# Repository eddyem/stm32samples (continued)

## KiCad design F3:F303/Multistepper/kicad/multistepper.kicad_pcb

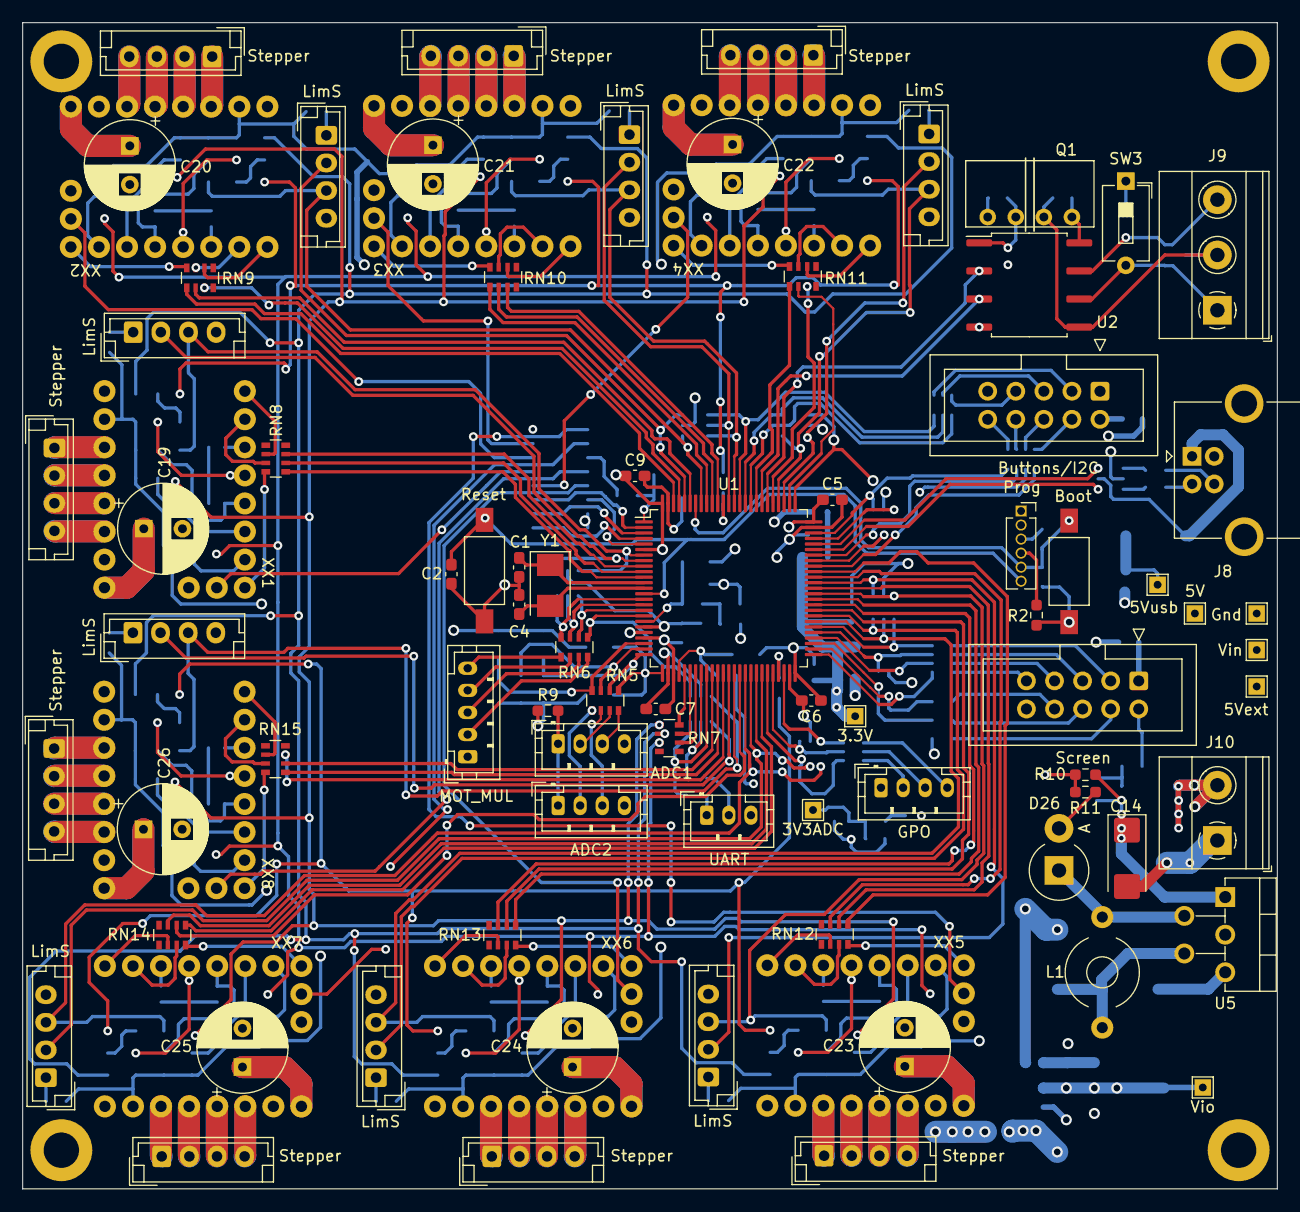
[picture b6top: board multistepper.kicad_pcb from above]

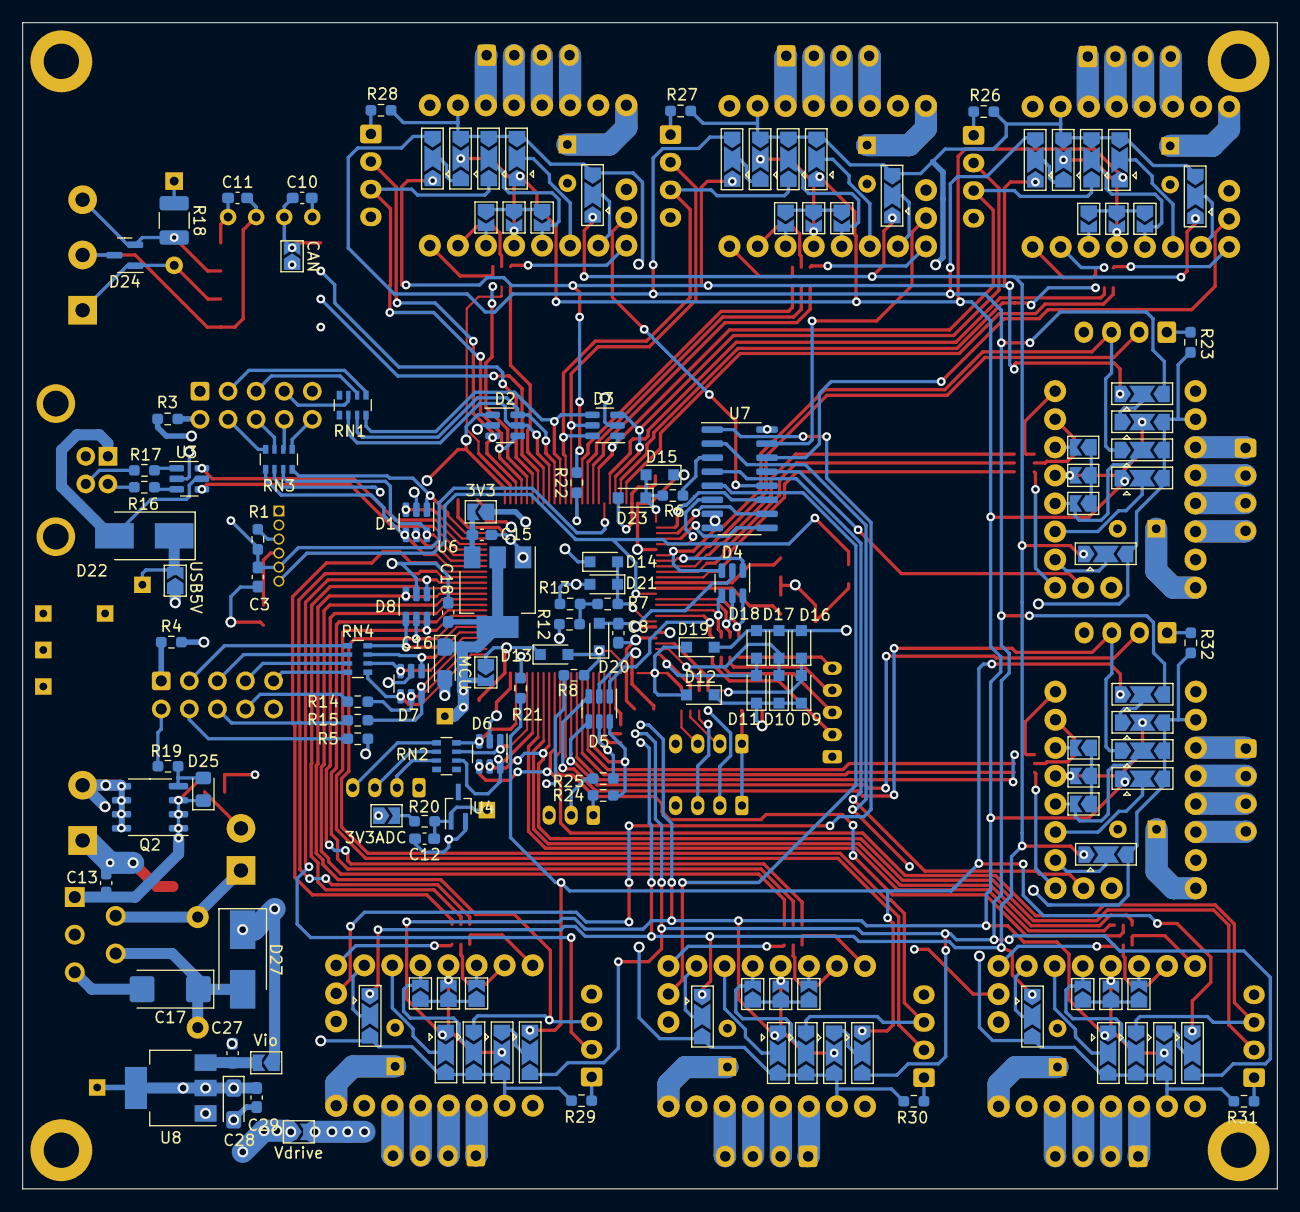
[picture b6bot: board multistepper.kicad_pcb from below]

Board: 4 copper layers, 113.5 x 105.5 mm, 236 parts (148 on the bottom side), 282 nets.

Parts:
C1, C4: 12; C_0603_1608Metric_Pad1.08x0.95mm_HandSolder
C2, C3, C5, C6, C7, C8, C9, C13, C15, C18, C27, C29: 0.1; C_0603_1608Metric_Pad1.08x0.95mm_HandSolder
C10, C11, C12: 1u; C_0603_1608Metric_Pad1.08x0.95mm_HandSolder
C14: 47u 35V; CP_EIA-6032-28_Kemet-C_Pad2.25x2.35mm_HandSolder
C16, C28: 47u 6V; CP_EIA-3216-18_Kemet-A_Pad1.58x1.35mm_HandSolder
C17: 47u 10V; CP_EIA-6032-28_Kemet-C_Pad2.25x2.35mm_HandSolder
C19, C20, C21, C22, C23, C24, C25, C26: 100u 35V; CP_Radial_D8.0mm_P3.50mm
D1, D2, D3, D4, D5, D6, D7, D8: SP0505BAHT; SOT-23-6
D9, D10, D11, D12, D13, D14, D15, D16, D17, D18, D19, D20, D21, D23: SS14; D_SOD-323_HandSoldering
D22, D27: MBRS130L; D_SMB_Handsoldering
D24: PESD1CAN; SOT-23
D25: MM3Z7V5; D_0805_2012Metric_Pad1.15x1.40mm_HandSolder
D26: 1N5822; D_DO-201_P3.81mm_Vertical_AnodeUp
H1, H2, H3, H4: MountingHole; MountingHole_3.2mm_M3_DIN965_Pad
J1: Prog; PinSocket_1x06_P1.27mm_Vertical
J2: Buttons/I2C; IDC-Header_2x05_P2.54mm_Vertical
J3: Screen; IDC-Header_2x05_P2.54mm_Vertical
J4: ADC2; JST_PH_B4B-PH-K_1x04_P2.00mm_Vertical
J5: ADC1; JST_PH_B4B-PH-K_1x04_P2.00mm_Vertical
J6: MOT_MUL; JST_PH_B5B-PH-K_1x05_P2.00mm_Vertical
J7: GPO; JST_PH_B4B-PH-K_1x04_P2.00mm_Vertical
J8: USB_B; USB_B_OST_USB-B1HSxx_Horizontal
J9: Screw_Terminal_01x03; TerminalBlock_Phoenix_MKDS-1,5-3_1x03_P5.00mm_Horizontal
J10: Screw_Terminal_01x02; TerminalBlock_Phoenix_MKDS-1,5-2_1x02_P5.00mm_Horizontal
J11, J14, J16, J18, J20, J22, J24, J26: LimS; JST_EH_B4B-EH-A_1x04_P2.50mm_Vertical
J12, J15, J17, J19, J21, J23, J25, J27: Stepper; JST_EH_B4B-EH-A_1x04_P2.50mm_Vertical
J13: UART; JST_PH_B3B-PH-K_1x03_P2.00mm_Vertical
JP1: CAN; SolderJumper-2_P1.3mm_Open_TrianglePad1.0x1.5mm
JP2: USB5V; SolderJumper-2_P1.3mm_Open_TrianglePad1.0x1.5mm
JP3: MCU; SolderJumper-2_P1.3mm_Open_TrianglePad1.0x1.5mm
JP4: 3V3ADC; SolderJumper-2_P1.3mm_Open_TrianglePad1.0x1.5mm
JP5: 3V3; SolderJumper-2_P1.3mm_Open_TrianglePad1.0x1.5mm
JP6: Vdrive; SolderJumper-2_P1.3mm_Open_TrianglePad1.0x1.5mm
JP7: Vio; SolderJumper-2_P1.3mm_Open_TrianglePad1.0x1.5mm
JP8, JP9, JP10, JP11, JP12, JP16, JP17, JP18, JP19, JP20, JP24, JP25, JP26, JP27, JP28, JP32, JP33, JP34, JP35, JP36, JP40, JP41, JP42, JP43, JP44, JP48, JP49, JP50, JP51, JP52, JP56, JP57, JP58, JP59, JP60, JP64, JP65, JP66, JP67, JP68: SolderJumper_3_Open; SolderJumper-3_P2.0mm_Open_TrianglePad1.0x1.5mm
JP13, JP14, JP15, JP21, JP22, JP23, JP29, JP30, JP31, JP37, JP38, JP39, JP45, JP46, JP47, JP53, JP54, JP55, JP61, JP62, JP63, JP69, JP70, JP71: SolderJumper_2_Bridged; SolderJumper-2_P1.3mm_Open_TrianglePad1.0x1.5mm
L1: 100u; L_Toroid_Horizontal_D6.5mm_P10.00mm_Diameter7-5mm_Amidon-T25
Q1: B0505S; B0x0xS
Q2: IRF9310; SO-8_3.9x4.9mm_P1.27mm
R1, R11: 10k; R_0603_1608Metric_Pad0.98x0.95mm_HandSolder
R2, R3, R9, R16, R17, R24, R25: 22; R_0603_1608Metric_Pad0.98x0.95mm_HandSolder
R4: 7.5; R_0603_1608Metric_Pad0.98x0.95mm_HandSolder
R5: 5.1; R_0603_1608Metric_Pad0.98x0.95mm_HandSolder
R6, R7, R8, R14, R15: 330; R_0603_1608Metric_Pad0.98x0.95mm_HandSolder
R10: 91k; R_0603_1608Metric_Pad0.98x0.95mm_HandSolder
R12, R13: 47k; R_0603_1608Metric_Pad0.98x0.95mm_HandSolder
R18: 120; R_1210_3225Metric_Pad1.30x2.65mm_HandSolder
R19, R20: 4k7; R_0603_1608Metric_Pad0.98x0.95mm_HandSolder
R21, R22, R23, R26, R27, R28, R29, R30, R31, R32: 100; R_0603_1608Metric_Pad0.98x0.95mm_HandSolder
RN1, RN2, RN3, RN4, RN5, RN6, RN7, RN8, RN9, RN10, RN11, RN12, RN13, RN14, RN15: 330; R_Array_Convex_4x0603
SW1: Reset; SW_SPST_FSMSM
SW2: Boot; SW_SPST_FSMSM
SW3: SW_DIP_x01; SW_DIP_SPSTx01_Slide_6.7x4.1mm_W7.62mm_P2.54mm_LowProfile
TP1: 5Vusb; TestPoint_THTPad_1.5x1.5mm_Drill0.7mm
TP2: Vin; TestPoint_THTPad_1.5x1.5mm_Drill0.7mm
TP3: Gnd; TestPoint_THTPad_1.5x1.5mm_Drill0.7mm
TP4: 5Vext; TestPoint_THTPad_1.5x1.5mm_Drill0.7mm
TP5: 3.3V; TestPoint_THTPad_1.5x1.5mm_Drill0.7mm
TP6: 3V3ADC; TestPoint_THTPad_1.5x1.5mm_Drill0.7mm
TP7: 5V; TestPoint_THTPad_1.5x1.5mm_Drill0.7mm
TP8: Vio; TestPoint_THTPad_1.5x1.5mm_Drill0.7mm
U1: STM32F303VDTx; LQFP-100_14x14mm_P0.5mm
U2: ISO1050DUB; SOP-8_6.62x9.15mm_P2.54mm
U3: USBLC6-2SC6; SOT-23-6
U4: LM4050A(b)EX3-3.3; SOT-323_SC-70_Handsoldering
U5: LM2576-5.0; TO-220-5_P3.4x3.7mm_StaggerEven_Lead3.8mm_Vertical
U6, U8: LM1117-3.3; SOT-223-3_TabPin2
U7: 74HC4051; SOIC-16_3.9x9.9mm_P1.27mm
XX1, XX2, XX3, XX4, XX5, XX6, XX7, XX8: stepper_module
Y1: NX5032GA-8MHz; Crystal_SMD_5032-2Pin_5.0x3.2mm

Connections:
+3.3VADC: C12.1, R20.1, TP6.1, U1.21 (VREF+), U4.1 (K)
+3V3: C16.1, C18.1, JP3.2 (B), R3.2, R4.2, TP5.1, U6.2 (VO)
+5V: D27.1 (K), JP1.1 (A), JP2.1 (A), JP4.1 (A), JP5.1 (A), JP7.1 (A), R5.1, R12.2, TP7.1
/CANH: D24.2 (K), J9.3, R18.2, U2.7 (CANH)
/CANL: D24.1 (K), J9.1, SW3.2, U2.6 (CANL)
/MCU base/A0: D9.2 (A), D16.1 (K), RN5.8 (R1.2), U1.23 (PA0)
/MCU base/A1: D10.2 (A), D17.1 (K), RN5.7 (R2.2), U1.24 (PA1)
/MCU base/A2: D11.2 (A), D18.1 (K), RN5.6 (R3.2), U1.25 (PA2)
/MCU base/A3: D12.2 (A), D19.1 (K), RN5.5 (R4.2), U1.26 (PA3)
/MCU base/A4: D13.2 (A), D20.1 (K), R8.1, U1.29 (PA4)
/MCU base/A5: D14.2 (A), D21.1 (K), R7.2, U1.19 (PF2)
/MCU base/BOOT0: C3.1, J1.5, R1.1, SW2.1, U1.94 (BOOT0)
/MCU base/BTN0: D1.4 (K), RN3.1 (R1.1), U1.67 (PA8)
/MCU base/BTN1: D1.5 (K), RN3.2 (R2.1), U1.68 (PA9)
/MCU base/BTN2_SDA: D1.6 (K), RN3.3 (R3.1), U1.69 (PA10)
/MCU base/BTN3_SCL: D1.1 (K), RN3.4 (R4.1), U1.73 (PF6)
/MCU base/BTN4: D2.5 (K), RN1.6 (R3.2), U1.84 (PD3)
/MCU base/BTN5: D2.6 (K), RN1.7 (R2.2), U1.85 (PD4)
/MCU base/BTN6: D3.4 (K), RN1.8 (R1.2), U1.86 (PD5)
/MCU base/Diagn: D15.2 (A), D23.1 (K), R6.2, U1.1 (PE2)
/MCU base/MOT_MUL0: D4.6 (K), RN6.8 (R1.2), U1.15 (PC0)
/MCU base/MOT_MUL1: D4.5 (K), RN6.7 (R2.2), U1.16 (PC1)
/MCU base/MOT_MUL2: D4.4 (K), RN6.6 (R3.2), U1.17 (PC2)
/MCU base/MOT_MUL_EN: D5.1 (K), RN6.5 (R4.2), U1.18 (PC3)
/MCU base/NRST: C2.1, J1.6, SW1.1, U1.14 (NRST)
/MCU base/OSC_IN: C1.1, U1.12 (PF0), Y1.1
/MCU base/OSC_OUT: C4.1, U1.13 (PF1), Y1.2
/MCU base/OUT0: D6.3 (K), RN2.8 (R1.2), U1.48 (PB11)
/MCU base/OUT1: D6.1 (K), RN2.7 (R2.2), U1.46 (PE15)
/MCU base/OUT2: D6.6 (K), RN2.6 (R3.2), U1.45 (PE14)
/MCU base/SCRN_CS: D8.4 (K), RN4.4 (R4.1), U1.56 (PD9)
/MCU base/SCRN_DCRS: D7.4 (K), RN4.1 (R1.1), U1.51 (PB12)
/MCU base/SCRN_MISO: D7.6 (K), R15.1, U1.53 (PB14)
/MCU base/SCRN_MOSI: D7.3 (K), RN4.2 (R2.1), U1.54 (PB15)
/MCU base/SCRN_RST: D7.1 (K), RN4.3 (R3.1), U1.55 (PD8)
/MCU base/SCRN_SCK: D7.5 (K), R14.1, U1.52 (PB13)
/MCU base/SWCLK: D2.1 (K), J1.1, U1.76 (PA14)
/MCU base/SWDIO: D1.3 (K), J1.2, U1.72 (PA13)
/MCU base/USART1_RX: D5.6 (K), R24.1, U1.34 (PC5)
/MCU base/USART1_TX: D5.5 (K), R25.1, U1.33 (PC4)
/Motors/DIAG0: U7.13 (Y0), XX1.17 (DIAG)
/Motors/DIAG1: U7.14 (Y1), XX2.17 (DIAG)
/Motors/DIAG2: U7.15 (Y2), XX3.17 (DIAG)
/Motors/DIAG3: U7.12 (Y3), XX4.17 (DIAG)
/Motors/DIAG4: U7.1 (Y4), XX5.17 (DIAG)
/Motors/DIAG5: U7.5 (Y5), XX6.17 (DIAG)
/Motors/DIAG6: U7.2 (Y6), XX7.17 (DIAG)
/Motors/DIAG7: U7.4 (Y7), XX8.17 (DIAG)
/Motors/MISO: JP9.3 (B), JP17.3 (B), JP25.3 (B), JP33.3 (B), JP41.3 (B), JP49.3 (B), JP57.3 (B), JP65.3 (B), RN7.2 (R2.1)
/Motors/MOSI: JP10.1 (A), JP18.1 (A), JP26.1 (A), JP34.1 (A), JP42.1 (A), JP50.1 (A), JP58.1 (A), JP66.1 (A), RN7.3 (R3.1)
/Motors/SCK: JP11.1 (A), JP19.1 (A), JP27.1 (A), JP35.1 (A), JP43.1 (A), JP51.1 (A), JP59.1 (A), JP67.1 (A), RN7.1 (R1.1)
/Motors/USART0-3: JP9.1 (A), JP17.1 (A), JP25.1 (A), JP33.1 (A), R22.2
/Motors/USART4-7: JP41.1 (A), JP49.1 (A), JP57.1 (A), JP65.1 (A), R21.2
/Motors/Vm: C19.1, C20.1, C21.1, C22.1, C23.1, C24.1, C25.1, C26.1, JP6.2 (B), XX1.16 (Vmot), XX2.16 (Vmot), XX3.16 (Vmot), XX4.16 (Vmot), XX5.16 (Vmot), XX6.16 (Vmot), XX7.16 (Vmot), XX8.16 (Vmot)
/Motors/stepper_M1/CLK: JP15.2 (B), XX1.6 (CLK)
/Motors/stepper_M1/DIRx: RN8.2 (R2.1), XX1.8 (DIR)
/Motors/stepper_M1/MS1: JP10.2 (C), XX1.2 (MS1)
/Motors/stepper_M1/MS2: JP11.2 (C), XX1.3 (MS2)
/Motors/stepper_M1/SPR: JP12.2 (C), JP13.2 (B), XX1.4 (SPREAD)
/Motors/stepper_M1/STEPx: RN8.3 (R3.1), XX1.7 (STEP)
/Motors/stepper_M1/U: JP8.2 (C), JP14.2 (B), XX1.5 (PDN_UART)
/Motors/stepper_M1/~ENx: RN8.4 (R4.1), XX1.1 (~EN)
/Motors/stepper_M2/CLK: JP23.2 (B), XX2.6 (CLK)
/Motors/stepper_M2/DIRx: RN9.2 (R2.1), XX2.8 (DIR)
/Motors/stepper_M2/MS1: JP18.2 (C), XX2.2 (MS1)
/Motors/stepper_M2/MS2: JP19.2 (C), XX2.3 (MS2)
/Motors/stepper_M2/SPR: JP20.2 (C), JP21.2 (B), XX2.4 (SPREAD)
/Motors/stepper_M2/STEPx: RN9.3 (R3.1), XX2.7 (STEP)
/Motors/stepper_M2/U: JP16.2 (C), JP22.2 (B), XX2.5 (PDN_UART)
/Motors/stepper_M2/~ENx: RN9.4 (R4.1), XX2.1 (~EN)
/Motors/stepper_M3/CLK: JP31.2 (B), XX3.6 (CLK)
/Motors/stepper_M3/DIRx: RN10.2 (R2.1), XX3.8 (DIR)
/Motors/stepper_M3/MS1: JP26.2 (C), XX3.2 (MS1)
/Motors/stepper_M3/MS2: JP27.2 (C), XX3.3 (MS2)
/Motors/stepper_M3/SPR: JP28.2 (C), JP29.2 (B), XX3.4 (SPREAD)
/Motors/stepper_M3/STEPx: RN10.3 (R3.1), XX3.7 (STEP)
/Motors/stepper_M3/U: JP24.2 (C), JP30.2 (B), XX3.5 (PDN_UART)
/Motors/stepper_M3/~ENx: RN10.4 (R4.1), XX3.1 (~EN)
/Motors/stepper_M4/CLK: JP39.2 (B), XX4.6 (CLK)
/Motors/stepper_M4/DIRx: RN11.2 (R2.1), XX4.8 (DIR)
/Motors/stepper_M4/MS1: JP34.2 (C), XX4.2 (MS1)
/Motors/stepper_M4/MS2: JP35.2 (C), XX4.3 (MS2)
/Motors/stepper_M4/SPR: JP36.2 (C), JP37.2 (B), XX4.4 (SPREAD)
/Motors/stepper_M4/STEPx: RN11.3 (R3.1), XX4.7 (STEP)
/Motors/stepper_M4/U: JP32.2 (C), JP38.2 (B), XX4.5 (PDN_UART)
/Motors/stepper_M4/~ENx: RN11.4 (R4.1), XX4.1 (~EN)
/Motors/stepper_M5/CLK: JP47.2 (B), XX5.6 (CLK)
/Motors/stepper_M5/DIRx: RN12.2 (R2.1), XX5.8 (DIR)
/Motors/stepper_M5/MS1: JP42.2 (C), XX5.2 (MS1)
/Motors/stepper_M5/MS2: JP43.2 (C), XX5.3 (MS2)
/Motors/stepper_M5/SPR: JP44.2 (C), JP45.2 (B), XX5.4 (SPREAD)
/Motors/stepper_M5/STEPx: RN12.3 (R3.1), XX5.7 (STEP)
/Motors/stepper_M5/U: JP40.2 (C), JP46.2 (B), XX5.5 (PDN_UART)
/Motors/stepper_M5/~ENx: RN12.4 (R4.1), XX5.1 (~EN)
/Motors/stepper_M6/CLK: JP55.2 (B), XX6.6 (CLK)
/Motors/stepper_M6/DIRx: RN13.2 (R2.1), XX6.8 (DIR)
/Motors/stepper_M6/MS1: JP50.2 (C), XX6.2 (MS1)
/Motors/stepper_M6/MS2: JP51.2 (C), XX6.3 (MS2)
/Motors/stepper_M6/SPR: JP52.2 (C), JP53.2 (B), XX6.4 (SPREAD)
/Motors/stepper_M6/STEPx: RN13.3 (R3.1), XX6.7 (STEP)
/Motors/stepper_M6/U: JP48.2 (C), JP54.2 (B), XX6.5 (PDN_UART)
/Motors/stepper_M6/~ENx: RN13.4 (R4.1), XX6.1 (~EN)
/Motors/stepper_M7/CLK: JP63.2 (B), XX7.6 (CLK)
/Motors/stepper_M7/DIRx: RN14.2 (R2.1), XX7.8 (DIR)
/Motors/stepper_M7/MS1: JP58.2 (C), XX7.2 (MS1)
/Motors/stepper_M7/MS2: JP59.2 (C), XX7.3 (MS2)
/Motors/stepper_M7/SPR: JP60.2 (C), JP61.2 (B), XX7.4 (SPREAD)
/Motors/stepper_M7/STEPx: RN14.3 (R3.1), XX7.7 (STEP)
/Motors/stepper_M7/U: JP56.2 (C), JP62.2 (B), XX7.5 (PDN_UART)
/Motors/stepper_M7/~ENx: RN14.4 (R4.1), XX7.1 (~EN)
/Motors/stepper_M8/CLK: JP71.2 (B), XX8.6 (CLK)
/Motors/stepper_M8/DIRx: RN15.2 (R2.1), XX8.8 (DIR)
/Motors/stepper_M8/MS1: JP66.2 (C), XX8.2 (MS1)
/Motors/stepper_M8/MS2: JP67.2 (C), XX8.3 (MS2)
/Motors/stepper_M8/SPR: JP68.2 (C), JP69.2 (B), XX8.4 (SPREAD)
/Motors/stepper_M8/STEPx: RN15.3 (R3.1), XX8.7 (STEP)
/Motors/stepper_M8/U: JP64.2 (C), JP70.2 (B), XX8.5 (PDN_UART)
/Motors/stepper_M8/~ENx: RN15.4 (R4.1), XX8.1 (~EN)
/VB: D22.2 (A), J8.1 (VBUS), U3.5 (VBUS)
ADC0: J4.2, RN5.1 (R1.1)
ADC1: J4.3, RN5.2 (R2.1)
ADC2: J5.2, RN5.3 (R3.1)
ADC3: J5.3, RN5.4 (R4.1)
ADC4: R8.2, R10.1, R11.2
ADC5: R7.1, R12.1, R13.2
CAN_RX: U1.81 (PD0), U2.2 (RXD)
CAN_TX: U1.82 (PD1), U2.3 (TXD)
DIAGNOST: R6.1, U7.3 (Z)
Earth: C11.2, D24.3 (O), J9.2, Q1.3 (0V), U2.5 (GND2)
GND: C1.2, C2.2, C4.2, C5.2, C6.2, C7.2, C8.2, C9.2, C10.2, C12.2, C13.2, C14.2, C15.2, C16.2, C17.2, C18.2, C19.2, C20.2, C21.2, C22.2, C23.2, C24.2, C25.2, C26.2, C27.2, C28.2, C29.2, D1.2 (A), D2.2 (A), D3.2 (A), D4.2 (A), D5.2 (A), D6.2 (A), D7.2 (A), D8.2 (A), D16.2 (A), D17.2 (A), D18.2 (A), D19.2 (A), D20.2 (A), D21.2 (A), D23.2 (A), D26.2 (A), J1.3, J2.1, J2.9, J3.2, J3.10, J4.4, J5.4, J6.1, J7.1, J8.4 (GND), J8.5 (Shield), J10.1, J11.4, J13.3, J14.4, J16.4, J18.4, J20.4, J22.4, J24.4, J26.4, Q1.1 (GND), R1.2, R11.1, R13.1, R19.2, SW1.2, TP3.1, U1.20 (VSSA), U1.27 (VSS), U1.49 (VSS), U1.74 (VSS), U1.99 (VSS), U2.4 (GND1), U3.2 (GND), U4.2 (A), U5.3 (GND), U5.5 (ON/OFF), U6.1 (GND), U7.7 (VEE), U7.8 (GND), U8.1 (GND), XX1.9 (GND), XX1.15 (GND), XX2.9 (GND), XX2.15 (GND), XX3.9 (GND), XX3.15 (GND), XX4.9 (GND), XX4.15 (GND), XX5.9 (GND), XX5.15 (GND), XX6.9 (GND), XX6.15 (GND), XX7.9 (GND), XX7.15 (GND), XX8.9 (GND), XX8.15 (GND)
M0_DIR: RN8.7 (R2.2), U1.9 (PC15)
M0_EN: RN8.5 (R4.2), U1.11 (PF10)
M0_L0: D4.1 (K), J11.2, U1.8 (PC14)
M0_L1: D4.3 (K), J11.3, JP12.1 (A), U1.7 (PC13)
M0_STEP: RN8.6 (R3.2), U1.10 (PF9)
M1_DIR: RN9.7 (R2.2), U1.97 (PE0)
M1_EN: RN9.5 (R4.2), U1.98 (PE1)
M1_L0: D3.3 (K), J14.2, U1.96 (PB9)
M1_L1: D3.1 (K), J14.3, JP20.1 (A), U1.93 (PB7)
M1_STEP: RN9.6 (R3.2), U1.95 (PB8)
M2_DIR: RN10.7 (R2.2), U1.90 (PB4)
M2_EN: RN10.5 (R4.2), U1.92 (PB6)
M2_L0: D3.5 (K), J16.2, U1.88 (PD7)
M2_L1: D3.6 (K), J16.3, JP28.1 (A), U1.87 (PD6)
M2_STEP: RN10.6 (R3.2), U1.91 (PB5)
M3_DIR: RN11.7 (R2.2), U1.80 (PC12)
M3_EN: RN11.5 (R4.2), U1.83 (PD2)
M3_L0: D2.3 (K), J18.2, U1.78 (PC10)
M3_L1: D2.4 (K), J18.3, JP36.1 (A), U1.79 (PC11)
M3_STEP: RN11.6 (R3.2), U1.77 (PA15)
M4_DIR: RN12.7 (R2.2), U1.65 (PC8)
M4_EN: RN12.5 (R4.2), U1.66 (PC9)
M4_L0: D8.1 (K), J20.2, U1.64 (PC7)
M4_L1: D8.3 (K), J20.3, JP44.1 (A), U1.62 (PD15)
M4_STEP: RN12.6 (R3.2), U1.63 (PC6)
M5_DIR: RN13.7 (R2.2), U1.60 (PD13)
M5_EN: RN13.5 (R4.2), U1.61 (PD14)
M5_L0: D8.6 (K), J22.2, U1.58 (PD11)
M5_L1: D8.5 (K), J22.3, JP52.1 (A), U1.57 (PD10)
M5_STEP: RN13.6 (R3.2), U1.59 (PD12)
M6_DIR: RN14.7 (R2.2), U1.43 (PE12)
M6_EN: RN14.5 (R4.2), U1.44 (PE13)
M6_L0: D6.5 (K), J24.2, U1.42 (PE11)
M6_L1: D6.4 (K), J24.3, JP60.1 (A), U1.41 (PE10)
M6_STEP: RN14.6 (R3.2), U1.40 (PE9)
M7_DIR: RN15.7 (R2.2), U1.37 (PB2)
M7_EN: RN15.5 (R4.2), U1.36 (PB1)
M7_L0: D5.4 (K), J26.2, U1.38 (PE7)
M7_L1: D5.3 (K), J26.3, JP68.1 (A), U1.39 (PE8)
M7_STEP: RN15.6 (R3.2), U1.35 (PB0)
MCU3v3: C3.2, C5.1, C6.1, C7.1, C8.1, C9.1, D9.1 (K), D10.1 (K), D11.1 (K), D12.1 (K), D13.1 (K), D14.1 (K), D15.1 (K), JP3.1 (A), R2.1, R9.1, SW2.2, U1.6 (VBAT), U1.22 (VDDA), U1.28 (VDD), U1.50 (VDD), U1.75 (VDD), U1.100 (VDD)
MUL0: U1.2 (PE3), U7.11 (S0)
MUL1: U1.3 (PE4), U7.10 (S1)
MUL2: U1.4 (PE5), U7.9 (S2)
MUL_EN: U1.5 (PE6), U7.6 (~E)
unnamed: C10.1, JP1.2 (B), Q1.2 (Vin), U2.1 (VCC1)
unnamed: C11.1, Q1.4 (+Vo), U2.8 (VCC2)
unnamed: C15.1, JP5.2 (B), U6.3 (VI)
unnamed: C17.1, D27.2 (A), L1.1, TP4.1, U5.4 (FB)
unnamed: C27.1, JP7.2 (B), U8.3 (VI)
unnamed: D22.1 (K), JP2.2 (B), TP1.1
unnamed: D25.2 (A), Q2.4 (G), R19.1
unnamed: D26.1 (K), L1.2, U5.2 (VOUT)
unnamed: J1.4, R2.2
unnamed: J2.2, R3.1
unnamed: J2.3, RN1.1 (R1.1)
unnamed: J2.4, RN3.8 (R1.2)
unnamed: J2.5, RN1.2 (R2.1)
unnamed: J2.6, RN3.7 (R2.2)
unnamed: J2.7, RN1.3 (R3.1)
unnamed: J2.8, RN3.6 (R3.2)
unnamed: J2.10, RN3.5 (R4.2)
unnamed: J3.1, R4.1
unnamed: J3.3, RN4.5 (R4.2)
unnamed: J3.4, R5.2
unnamed: J3.5, RN4.6 (R3.2)
unnamed: J3.6, R15.2
unnamed: J3.7, RN4.7 (R2.2)
unnamed: J3.8, R14.2
unnamed: J3.9, RN4.8 (R1.2)
unnamed: J4.1, J5.1, R9.2
unnamed: J6.2, RN6.4 (R4.1)
unnamed: J6.3, RN6.3 (R3.1)
unnamed: J6.4, RN6.2 (R2.1)
unnamed: J6.5, RN6.1 (R1.1)
unnamed: J7.2, RN2.3 (R3.1)
unnamed: J7.3, RN2.2 (R2.1)
unnamed: J7.4, RN2.1 (R1.1)
unnamed: J8.2 (D-), R16.1
unnamed: J8.3 (D+), R17.1
unnamed: J10.2, Q2.5 (D), Q2.6 (D), Q2.7 (D), Q2.8 (D)
unnamed: J11.1, R23.2
unnamed: J12.1, XX1.11 (M1B)
unnamed: J12.2, XX1.12 (M1A)
unnamed: J12.3, XX1.13 (M2A)
unnamed: J12.4, XX1.14 (M2B)
unnamed: J13.1, R24.2
unnamed: J13.2, R25.2
unnamed: J14.1, R26.2
unnamed: J15.1, XX2.11 (M1B)
unnamed: J15.2, XX2.12 (M1A)
unnamed: J15.3, XX2.13 (M2A)
unnamed: J15.4, XX2.14 (M2B)
unnamed: J16.1, R27.2
unnamed: J17.1, XX3.11 (M1B)
unnamed: J17.2, XX3.12 (M1A)
unnamed: J17.3, XX3.13 (M2A)
unnamed: J17.4, XX3.14 (M2B)
unnamed: J18.1, R28.2
unnamed: J19.1, XX4.11 (M1B)
unnamed: J19.2, XX4.12 (M1A)
unnamed: J19.3, XX4.13 (M2A)
unnamed: J19.4, XX4.14 (M2B)
unnamed: J20.1, R29.2
unnamed: J21.1, XX5.11 (M1B)
unnamed: J21.2, XX5.12 (M1A)
unnamed: J21.3, XX5.13 (M2A)
unnamed: J21.4, XX5.14 (M2B)
unnamed: J22.1, R30.2
unnamed: J23.1, XX6.11 (M1B)
unnamed: J23.2, XX6.12 (M1A)
unnamed: J23.3, XX6.13 (M2A)
unnamed: J23.4, XX6.14 (M2B)
unnamed: J24.1, R31.2
unnamed: J25.1, XX7.11 (M1B)
unnamed: J25.2, XX7.12 (M1A)
unnamed: J25.3, XX7.13 (M2A)
unnamed: J25.4, XX7.14 (M2B)
unnamed: J26.1, R32.2
unnamed: J27.1, XX8.11 (M1B)
unnamed: J27.2, XX8.12 (M1A)
unnamed: J27.3, XX8.13 (M2A)
unnamed: J27.4, XX8.14 (M2B)
unnamed: JP4.2 (B), R20.2
unnamed: JP8.1 (A), JP9.2 (C)
unnamed: JP13.1 (A), JP14.1 (A), JP15.1 (A)
unnamed: JP16.1 (A), JP17.2 (C)
unnamed: JP21.1 (A), JP22.1 (A), JP23.1 (A)
unnamed: JP24.1 (A), JP25.2 (C)
unnamed: JP29.1 (A), JP30.1 (A), JP31.1 (A)
unnamed: JP32.1 (A), JP33.2 (C)
unnamed: JP37.1 (A), JP38.1 (A), JP39.1 (A)
unnamed: JP40.1 (A), JP41.2 (C)
unnamed: JP45.1 (A), JP46.1 (A), JP47.1 (A)
unnamed: JP48.1 (A), JP49.2 (C)
unnamed: JP53.1 (A), JP54.1 (A), JP55.1 (A)
unnamed: JP56.1 (A), JP57.2 (C)
unnamed: JP61.1 (A), JP62.1 (A), JP63.1 (A)
unnamed: JP64.1 (A), JP65.2 (C)
unnamed: JP69.1 (A), JP70.1 (A), JP71.1 (A)
unnamed: R16.2, U3.3 (I/O2)
unnamed: R17.2, U3.1 (I/O1)
unnamed: R18.1, SW3.1
TMC_MISO: RN7.7 (R2.2), U1.31 (PA6)
TMC_MOSI: RN7.6 (R3.2), U1.32 (PA7)
TMC_SCK: RN7.8 (R1.2), U1.30 (PA5)
USART2_TX: R22.1, U1.89 (PB3)
USART3_TX: R21.1, U1.47 (PB10)
USB_DM: U1.70 (PA11), U3.4 (I/O2)
USB_DP: U1.71 (PA12), U3.6 (I/O1)
Vdrive: C13.1, C14.1, D25.1 (K), JP6.1 (A), Q2.1 (S), Q2.2 (S), Q2.3 (S), R10.2, TP2.1, U5.1 (VIN)
Vio: C28.1, C29.1, JP8.3 (B), JP10.3 (B), JP11.3 (B), JP12.3 (B), JP16.3 (B), JP18.3 (B), JP19.3 (B), JP20.3 (B), JP24.3 (B), JP26.3 (B), JP27.3 (B), JP28.3 (B), JP32.3 (B), JP34.3 (B), JP35.3 (B), JP36.3 (B), JP40.3 (B), JP42.3 (B), JP43.3 (B), JP44.3 (B), JP48.3 (B), JP50.3 (B), JP51.3 (B), JP52.3 (B), JP56.3 (B), JP58.3 (B), JP59.3 (B), JP60.3 (B), JP64.3 (B), JP66.3 (B), JP67.3 (B), JP68.3 (B), R23.1, R26.1, R27.1, R28.1, R29.1, R30.1, R31.1, R32.1, TP8.1, U7.16 (VCC), U8.2 (VO), XX1.10 (VIO), XX2.10 (VIO), XX3.10 (VIO), XX4.10 (VIO), XX5.10 (VIO), XX6.10 (VIO), XX7.10 (VIO), XX8.10 (VIO)

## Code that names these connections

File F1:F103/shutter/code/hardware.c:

/*
 * This file is part of the shutter project.
 * Copyright 2023 Edward V. Emelianov <edward.emelianoff@gmail.com>.
 *
 * This program is free software: you can redistribute it and/or modify
 * it under the terms of the GNU General Public License as published by
 * the Free Software Foundation, either version 3 of the License, or
 * (at your option) any later version.
 *
 * This program is distributed in the hope that it will be useful,
 * but WITHOUT ANY WARRANTY; without even the implied warranty of
 * MERCHANTABILITY or FITNESS FOR A PARTICULAR PURPOSE.  See the
 * GNU General Public License for more details.
 *
 * You should have received a copy of the GNU General Public License
 * along with this program.  If not, see <http://www.gnu.org/licenses/>.
 */

#include "adc.h"
#include "hardware.h"

static inline void iwdg_setup(){
    uint32_t tmout = 16000000;
    /* Enable the peripheral clock RTC */
    /* (1) Enable the LSI (40kHz) */
    /* (2) Wait while it is not ready */
    RCC->CSR |= RCC_CSR_LSION; /* (1) */
    while((RCC->CSR & RCC_CSR_LSIRDY) != RCC_CSR_LSIRDY){if(--tmout == 0) break;} /* (2) */
    /* Configure IWDG */
    /* (1) Activate IWDG (not needed if done in option bytes) */
    /* (2) Enable write access to IWDG registers */
    /* (3) Set prescaler by 64 (1.6ms for each tick) */
    /* (4) Set reload value to have a rollover each 2s */
    /* (5) Check if flags are reset */
    /* (6) Refresh counter */
    IWDG->KR = IWDG_START; /* (1) */
    IWDG->KR = IWDG_WRITE_ACCESS; /* (2) */
    IWDG->PR = IWDG_PR_PR_1; /* (3) */
    IWDG->RLR = 1250; /* (4) */
    tmout = 16000000;
    while(IWDG->SR){if(--tmout == 0) break;} /* (5) */
    IWDG->KR = IWDG_REFRESH; /* (6) */
}

/*
Pinout:
PB0 (pullup in) - hall (or reed switch) sensor input (active low) - opened shutter detector
PB11 (pullup in) - CCD or button input: open at low signal, close at high

PA3 (ADC in) - shutter voltage (approx 1/12 U)
PA5 (PP out) - TLE5205 IN2
PA6 (PP out) - TLE5205 IN1
PA7 (pullup in) - TLE5205 FB
PA10 (PP out) - USB pullup (active low)
PA11,12 - USB
PA13,14 - SWD
*/

static inline void gpio_setup(){
    // Enable clocks to the GPIO subsystems, turn on AFIO clocking to disable SWD/JTAG
    RCC->APB2ENR |= RCC_APB2ENR_IOPAEN | RCC_APB2ENR_IOPBEN | RCC_APB2ENR_AFIOEN;
    __DSB();
    // turn off SWJ/JTAG
//    AFIO->MAPR = AFIO_MAPR_SWJ_CFG_DISABLE;
    // AFIO->MAPR = AFIO_MAPR_SWJ_CFG_JTAGDISABLE; // for PA15
    // TLE5205 in OFF state
    // ADC (PA3), OD out (PA5,6), PU in (PA7)
    GPIOA->ODR = 1 << 7;
    SHTROFF();
    GPIOA->CRL = CRL(3, CNF_ANALOG|MODE_INPUT) | CRL(5, CNF_PPOUTPUT|MODE_SLOW) | CRL(6, CNF_PPOUTPUT|MODE_SLOW) |
                 CRL(7, CNF_PUDINPUT | MODE_INPUT);
    // USB pullup (PA10) - pushpull output
    GPIOA->CRH = CRH(8, CNF_PPOUTPUT | MODE_SLOW) | CRH(10, CNF_PPOUTPUT | MODE_SLOW);
    // hall/ccd
    GPIOB->ODR = 1 | 1<<11;
    GPIOB->CRL = CRL(0, CNF_PUDINPUT | MODE_INPUT);
    GPIOB->CRH = CRH(11, CNF_PUDINPUT | MODE_INPUT);
}

void hw_setup(){
    iwdg_setup();
    gpio_setup();
    adc_setup();
}

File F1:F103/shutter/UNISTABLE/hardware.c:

/*
 * This file is part of the shutter project.
 * Copyright 2023 Edward V. Emelianov <edward.emelianoff@gmail.com>.
 *
 * This program is free software: you can redistribute it and/or modify
 * it under the terms of the GNU General Public License as published by
 * the Free Software Foundation, either version 3 of the License, or
 * (at your option) any later version.
 *
 * This program is distributed in the hope that it will be useful,
 * but WITHOUT ANY WARRANTY; without even the implied warranty of
 * MERCHANTABILITY or FITNESS FOR A PARTICULAR PURPOSE.  See the
 * GNU General Public License for more details.
 *
 * You should have received a copy of the GNU General Public License
 * along with this program.  If not, see <http://www.gnu.org/licenses/>.
 */

#include "adc.h"
#include "flash.h"
#include "hardware.h"

TRUE_INLINE void iwdg_setup(){
    uint32_t tmout = 16000000;
    /* Enable the peripheral clock RTC */
    /* (1) Enable the LSI (40kHz) */
    /* (2) Wait while it is not ready */
    RCC->CSR |= RCC_CSR_LSION; /* (1) */
    while((RCC->CSR & RCC_CSR_LSIRDY) != RCC_CSR_LSIRDY){if(--tmout == 0) break;} /* (2) */
    /* Configure IWDG */
    /* (1) Activate IWDG (not needed if done in option bytes) */
    /* (2) Enable write access to IWDG registers */
    /* (3) Set prescaler by 64 (1.6ms for each tick) */
    /* (4) Set reload value to have a rollover each 2s */
    /* (5) Check if flags are reset */
    /* (6) Refresh counter */
    IWDG->KR = IWDG_START; /* (1) */
    IWDG->KR = IWDG_WRITE_ACCESS; /* (2) */
    IWDG->PR = IWDG_PR_PR_1; /* (3) */
    IWDG->RLR = 1250; /* (4) */
    tmout = 16000000;
    while(IWDG->SR){if(--tmout == 0) break;} /* (5) */
    IWDG->KR = IWDG_REFRESH; /* (6) */
}

/*
Pinout:
PB10 (pullup in) - CCD or button input (depends on settings)
PB11 (alternate: TIM2_CH4) - PWM output for shutter feeding
PB12 (pullup in) - hall (or reed switch) sensor input (opened/closed shutter detector)
PB13 (PP out) - USB pullup (active low)

PA3 (ADC in) - shutter voltage (approx 1/12 U)
PA9 (reserved) - USART1 Tx
PA10 (reserved) - USART1 Rx
PA11,12 - USB
PA13,14 - SWD
*/

TRUE_INLINE void gpio_setup(){
    // Enable clocks to the GPIO subsystems, turn on AFIO clocking to disable SWD/JTAG
    RCC->APB2ENR |= RCC_APB2ENR_IOPAEN | RCC_APB2ENR_IOPBEN | RCC_APB2ENR_AFIOEN;
    __DSB();
    // turn off SWJ/JTAG
//    AFIO->MAPR = AFIO_MAPR_SWJ_CFG_DISABLE;
    // AFIO->MAPR = AFIO_MAPR_SWJ_CFG_JTAGDISABLE; // for PA15
    GPIOA->CRL = CRL(3, CNF_ANALOG | MODE_INPUT);
    GPIOB->CRH = CRH(10, CNF_PUDINPUT | MODE_INPUT) | CRH(12, CNF_PUDINPUT | MODE_INPUT) |
                 CRH(13, CNF_PPOUTPUT | MODE_NORMAL);
    // if ccdactive==0 - shutter is closed when no output signals
    //GPIOB->ODR = ((the_conf.hallactive) ? 0: 1) | ((the_conf.ccdactive) ? 0 : 1<<11);
    GPIOB->ODR = (1<<10) | (1<<11); // PB10 & PB12 pullup
}

// TIM2_CH4 (36MHz) as PWM @ 65kHz
TRUE_INLINE void pwm_setup(){
    // remap TIM2_CH4 to PB11
    AFIO->MAPR = (AFIO->MAPR & ~AFIO_MAPR_TIM2_REMAP) |
                 AFIO_MAPR_TIM2_REMAP_PARTIALREMAP2;
    GPIOB->CRH |= CRH(11, CNF_AFPP | MODE_NORMAL);
    RCC->APB1ENR |= RCC_APB1ENR_TIM2EN;
    // 36 MHz / 100 / 65kHz = 5 ==> 7.2MHz with PWMfreq = 72kHz
    TIM2->PSC = 4;
    TIM2->ARR = 99;
    TIM2->CCR4 = 0; // turned off at start
    // mode1: active->inactive; CCR4 preload enable
    TIM2->CCMR2 = TIM_CCMR2_OC4M_2 | TIM_CCMR2_OC4M_1 | TIM_CCMR2_OC4PE;
    // enable PWM output
    TIM2->CCER = TIM_CCER_CC4E;
    // turn on and generate update event to refresh preloaded buffers
    TIM2->CR1 = TIM_CR1_CEN;
    TIM2->EGR = TIM_EGR_UG;
}

// set PWM to 0..100%, return 0 if `percent`>100
int set_pwm(uint32_t percent){
    if(percent > 100) return 0;
    TIM2->CCR4 = percent;
    return 1;
}

void hw_setup(){
    iwdg_setup();
    gpio_setup();
    adc_setup();
    pwm_setup();
}

uint32_t getShutterVoltage(){
    uint32_t val = getADCvoltage(CHSHTR);
    val *= the_conf.shtrVmul;
    return val / the_conf.shtrVdiv;
}

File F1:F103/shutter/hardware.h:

/*
 * This file is part of the shutter project.
 * Copyright 2022 Edward V. Emelianov <edward.emelianoff@gmail.com>.
 *
 * This program is free software: you can redistribute it and/or modify
 * it under the terms of the GNU General Public License as published by
 * the Free Software Foundation, either version 3 of the License, or
 * (at your option) any later version.
 *
 * This program is distributed in the hope that it will be useful,
 * but WITHOUT ANY WARRANTY; without even the implied warranty of
 * MERCHANTABILITY or FITNESS FOR A PARTICULAR PURPOSE.  See the
 * GNU General Public License for more details.
 *
 * You should have received a copy of the GNU General Public License
 * along with this program.  If not, see <http://www.gnu.org/licenses/>.
 */

#pragma once

#include <stm32f1.h>

#include "flash.h"

// PA7 - SHTR_FB
#define FBPORT      GPIOA
#define FBPIN       (1<<7)
// PA6, PA5 - SHTR_A, SHTR_B
#define SHTRPORT    GPIOA
#define SHTRAPOS    (6)
#define SHTRAPIN    (1<<SHTRAPOS)
#define SHTRBPOS    (5)
#define SHTRBPIN    (1<<SHTRBPOS)

#define CHKFB()     (FBPORT->IDR & FBPIN ? 0 : 1)
// open: 00
#define SHTROPEN()  do{SHTRPORT->BSRR = (SHTRAPIN | SHTRBPIN) << 16;}while(0)
// close: 01
#define SHTRCLOSE() do{SHTRPORT->BSRR = (SHTRAPIN << 16) | SHTRBPIN;}while(0)
// off: 10
#define SHTROFF()  do{SHTRPORT->BSRR = (SHTRBPIN << 16) | SHTRAPIN;}while(0)
// hiZ: 11
#define SHTRHIZ()   do{SHTRPORT->BSRR = SHTRAPIN | SHTRBPIN;}while(0)
#define SHTRSTATE() (((SHTRPORT->IDR & SHTRAPIN) >> (SHTRAPOS-1)) | ((SHTRPORT->IDR & SHTRBPIN) >> SHTRBPOS))
// states of TLE5205
typedef enum{
    REG_OPEN,
    REG_CLOSE,
    REG_OFF,
    REG_HIZ
} regul_state;

// PB0 - hall (==1 when opened), PB11 - CCD (active low)
#define BTNPORT     GPIOB
#define HALLPIN     (1<<0)
#define CCDPIN      (1<<11)
#define CHKHALL()   ((HALLPIN == (BTNPORT->IDR & HALLPIN)) == the_conf.hallactive)
#define CHKCCD()    ((CCDPIN == (BTNPORT->IDR & CCDPIN)) == the_conf.ccdactive)

extern volatile uint32_t Tms;

void hw_setup();
uint32_t getShutterVoltage();
